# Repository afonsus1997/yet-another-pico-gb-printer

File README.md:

# Yet Another Pico GB Printer

## Acknowledgements 
Based on the [The-TinyGB-Printer](https://github.com/Raphael-Boichot/The-TinyGB-Printer) by [Raphael-Boichot](https://github.com/Raphael-Boichot)

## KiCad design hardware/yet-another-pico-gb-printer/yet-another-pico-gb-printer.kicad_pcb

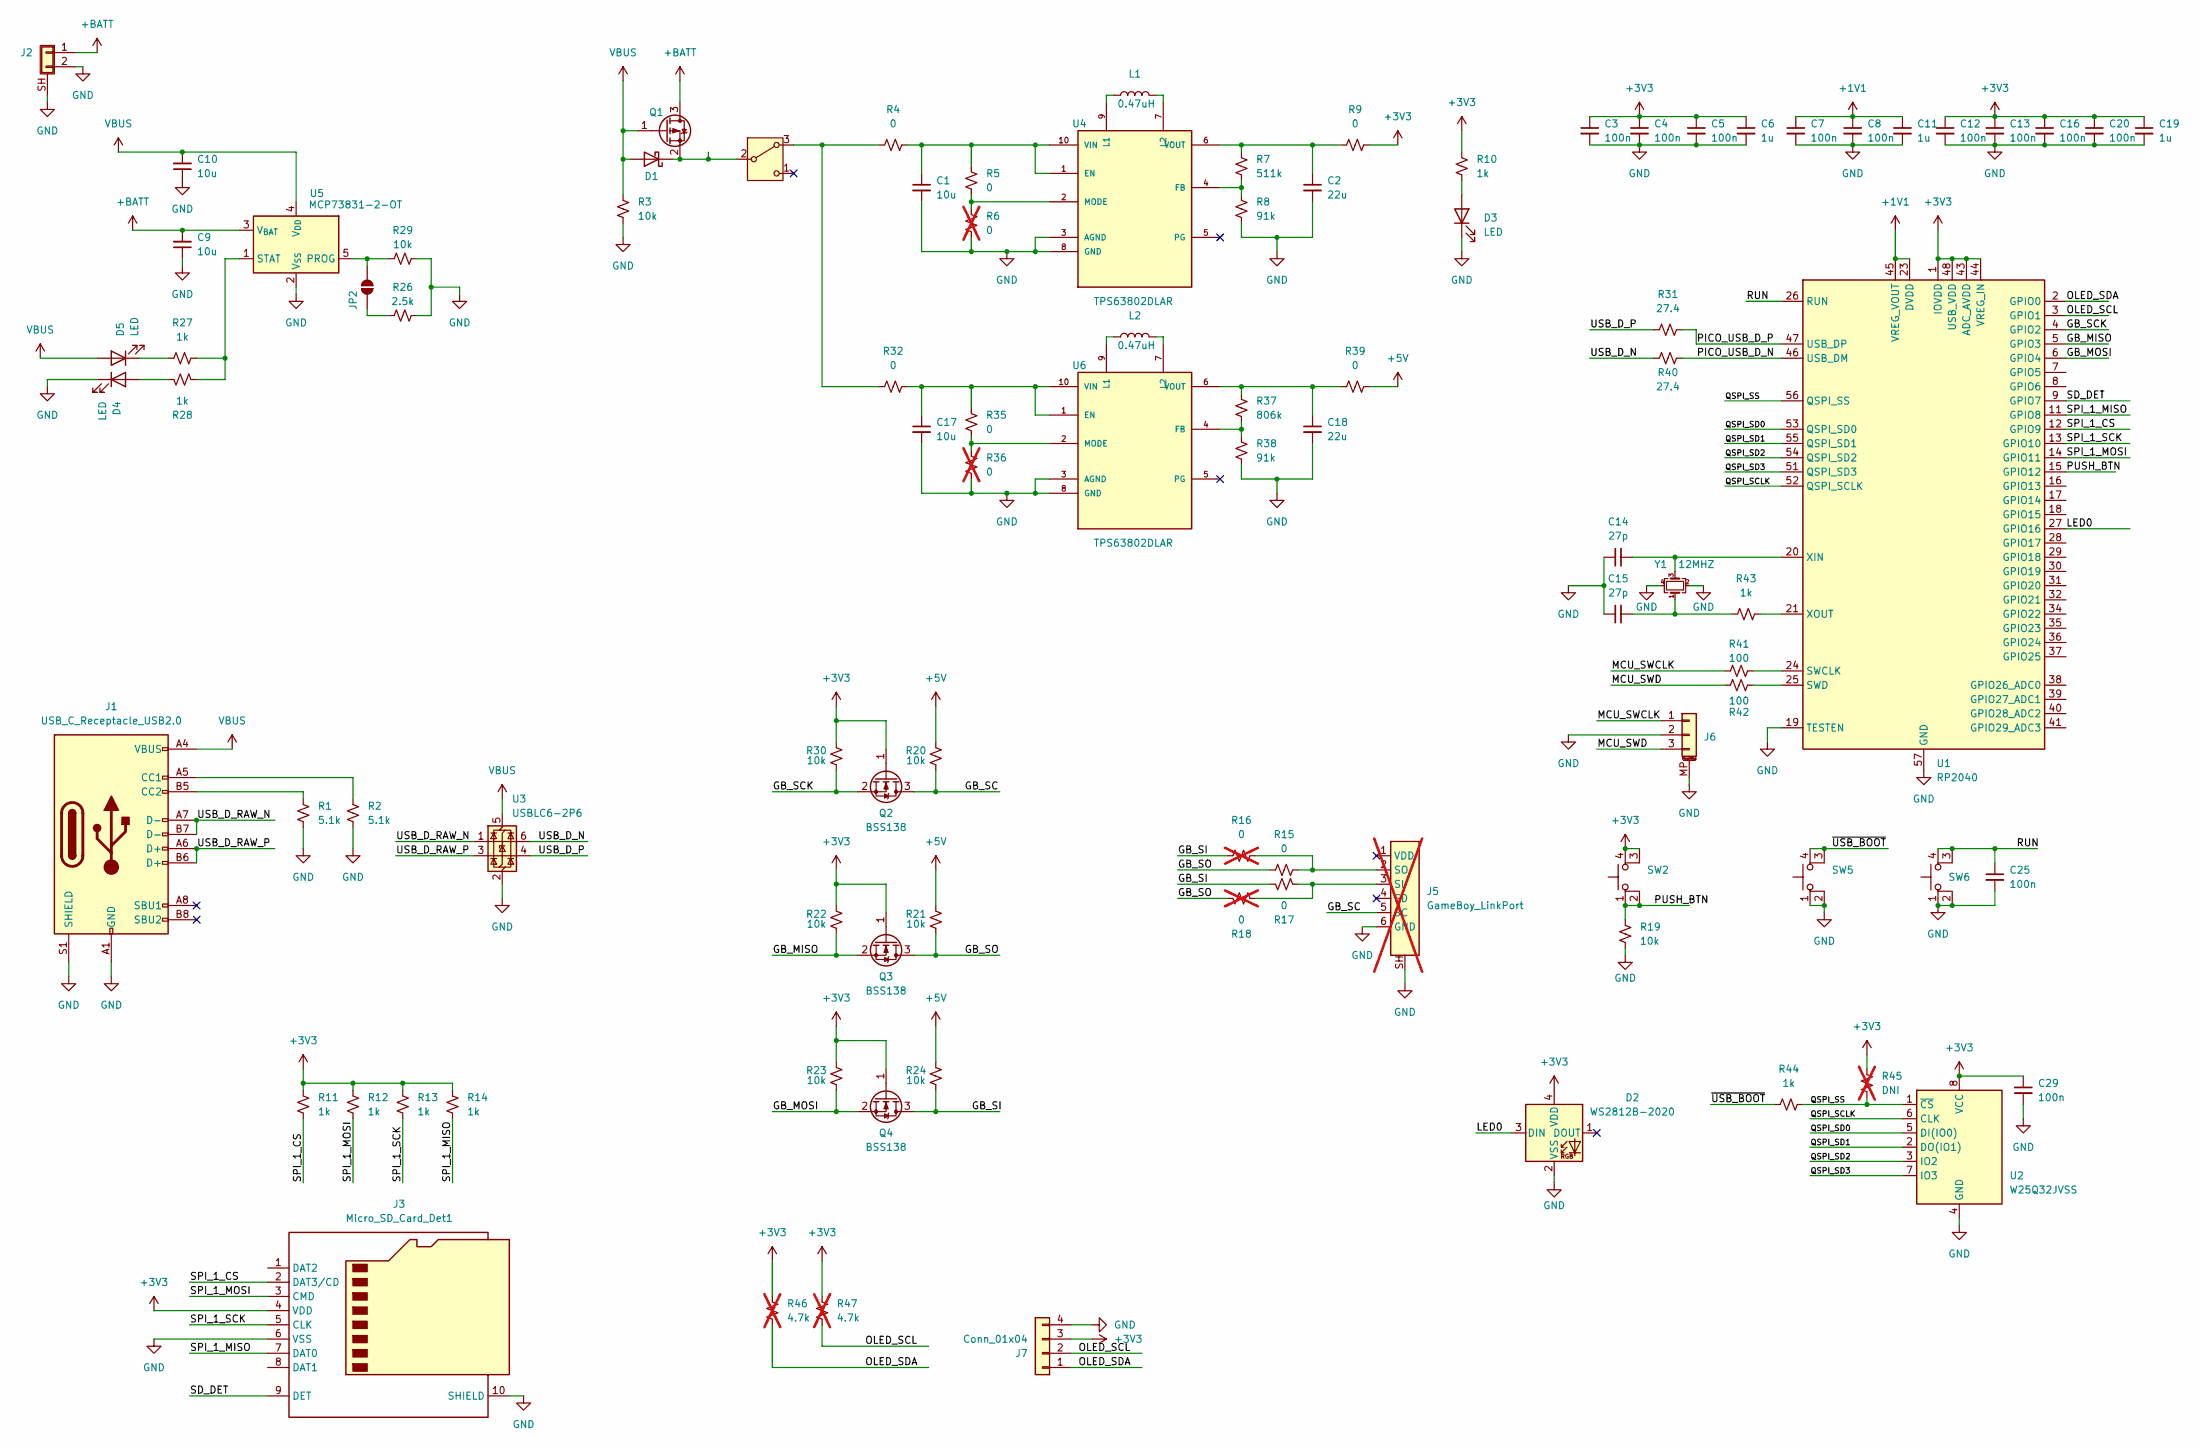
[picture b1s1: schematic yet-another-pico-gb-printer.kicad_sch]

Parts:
C1, C9, C10, C17: 10u; C_0603_1608Metric; LCSC C95839
C2, C18: 22u; C_0603_1608Metric; LCSC C59461
C3, C4, C5, C7, C8, C12, C13, C16, C20, C29: 100n; C_0402_1005Metric; LCSC C60474
C6, C11, C19: 1u; C_0402_1005Metric; LCSC C14445
C14, C15: 27p; C_0603_1608Metric; LCSC C107002
C25: 100n; C_0603_1608Metric; LCSC C60474
D1: D_Schottky; D_SOD-123F; LCSC C50553
D2: WS2812B-2020; LED_WS2812B-2020_PLCC4_2.0x2.0mm; LCSC C965555
D3, D4, D5: LED; LED_0603_1608Metric; LCSC C434424
J1: USB_C_Receptacle_USB2.0; USB_C_Receptacle_HCTL_HC-TYPE-C-16P-01A; LCSC C2894897
J2: Conn_01x02_Shielded; CONN-SMD_P2.00_S2B-PH-SM4-TB-LF-SN; LCSC C295747
J3: Micro_SD_Card_Det1; J_sd_micro_socket_no_holes; LCSC C7529389
J5: GameBoy_LinkPort; GBA-LINK; not fitted
J6: Conn_01x03_MountingPin; JST_SH_SM03B-SRSS-TB_1x03-1MP_P1.00mm_Horizontal; LCSC C160403
J7: Conn_01x04; OLED_SSD1306_128x32_0.91
JP2: SolderJumper_2_Open; SolderJumper-2_P1.3mm_Open_Pad1.0x1.5mm
L1, L2: 0.47uH; L_Wurth_WE-LQSH-2010; LCSC C89446
Q1: DMG3415U; SOT-23; LCSC C96616
Q2, Q3, Q4: BSS138; SOT-23; LCSC C5337205
R1, R2: 5.1k; R_0402_1005Metric; LCSC C105872
R3, R19, R20, R21, R22, R23, R24, R29, R30: 10k; R_0402_1005Metric; LCSC C60490
R4, R5, R9, R15, R17, R32, R35, R39: 0; R_0402_1005Metric; LCSC C106231
R6, R16, R18, R36: 0; R_0402_1005Metric; LCSC C106231; not fitted
R7: 511k; R_0402_1005Metric; LCSC C5126239
R8, R38: 91k; R_0402_1005Metric; LCSC C852952
R10, R11, R12, R13, R14, R27, R28, R43, R44: 1k; R_0402_1005Metric; LCSC C11702
R26: 2.5k; R_0402_1005Metric; LCSC C145071
R31, R40: 27.4; R_0402_1005Metric; LCSC C172043
R37: 806k; R_0402_1005Metric; LCSC C3016043
R41, R42: 100; R_0402_1005Metric; LCSC C25076
R45: DNI; R_0402_1005Metric; not fitted
R46, R47: 4.7k; R_0603_1608Metric; LCSC C99782; not fitted
SW2: SW_MEC_5E; SW-SMD_4P-L5.2-W5.2-P3.70-LS6.4; LCSC C2686853
SW3: SW_SPDT_321; SW-SMD_K3-1280S-L1; LCSC C223845
SW5, SW6: SW_MEC_5E; SW_SKRPACE010; LCSC C139797
U1: RP2040; QFN-56-1EP_7x7mm_P0.4mm_EP3.2x3.2mm; LCSC C2040
U2: W25Q32JVSS; Winbond_USON-8-1EP_3x2mm_P0.5mm_EP0.2x1.6mm; LCSC C2843335
U3: USBLC6-2P6; SOT-666; LCSC C2827693
U4, U6: TPS63802DLAR; VREG_TPS63802DLAR; PARTREV B; LCSC C2845237
U5: MCP73831-2-OT; SOT-23-5; LCSC C625600
Y1: 12MHZ; Crystal_SMD_3225-4Pin_3.2x2.5mm; LCSC C5182760

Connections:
+1V1: C7.1, C8.1, C11.1, U1.23 (DVDD), U1.45 (VREG_VOUT), U1.50 (DVDD)
+3V3: C3.1, C4.1, C5.1, C6.1, C12.1, C13.1, C16.1, C19.1, C20.1, C29.1, D2.4 (VDD), J3.4 (VDD), J7.3, Q2.1 (G), Q3.1 (G), Q4.1 (G), R9.2, R10.2, R11.2, R12.2, R13.2, R14.2, R22.1, R23.1, R30.1, R45.1, R46.1, R47.1, SW2.3 (K), SW2.4 (A), U1.1 (IOVDD), U1.10 (IOVDD), U1.22 (IOVDD), U1.33 (IOVDD), U1.42 (IOVDD), U1.43 (ADC_AVDD), U1.44 (VREG_IN), U1.48 (USB_VDD), U1.49 (IOVDD), U2.8 (VCC)
+5V: R20.1, R21.1, R24.1, R39.2
+BATT: C9.2, J2.1, Q1.3 (D), U5.3 (V_{BAT})
/GB_MISO: Q3.2 (S), R22.2, U1.5 (GPIO3)
/GB_MOSI: Q4.2 (S), R23.2, U1.6 (GPIO4)
/GB_SC: J5.5 (SC), Q2.3 (D), R20.2
/GB_SCK: Q2.2 (S), R30.2, U1.4 (GPIO2)
/GB_SI: Q4.3 (D), R16.1, R17.1, R24.2
/GB_SO: Q3.3 (D), R15.1, R18.1, R21.2
/LED0: D2.3 (DIN), U1.27 (GPIO16)
/MCU_SWCLK: J6.1, R41.1
/MCU_SWD: J6.3, R42.1
/OLED_SCL: J7.2, R47.2, U1.3 (GPIO1)
/OLED_SDA: J7.1, R46.2, U1.2 (GPIO0)
/PICO_USB_D_N: R40.2, U1.46 (USB_DM)
/PICO_USB_D_P: R31.2, U1.47 (USB_DP)
/PUSH_BTN: R19.1, SW2.1, SW2.2, U1.15 (GPIO12)
/QSPI_SCLK: U1.52 (QSPI_SCLK), U2.6 (CLK)
/QSPI_SD0: U1.53 (QSPI_SD0), U2.5 (DI(IO0))
/QSPI_SD1: U1.55 (QSPI_SD1), U2.2 (DO(IO1))
/QSPI_SD2: U1.54 (QSPI_SD2), U2.3 (IO2)
/QSPI_SD3: U1.51 (QSPI_SD3), U2.7 (IO3)
/QSPI_SS: R44.2, R45.2, U1.56 (QSPI_SS), U2.1 (~CS)
/RUN: C25.1, SW6.3 (K), SW6.4 (A), U1.26 (RUN)
/SD_DET: J3.9 (DET), U1.9 (GPIO7)
/SPI_1_CS: J3.2 (DAT3/CD), R11.1, U1.12 (GPIO9)
/SPI_1_MISO: J3.7 (DAT0), R14.1, U1.11 (GPIO8)
/SPI_1_MOSI: J3.3 (CMD), R12.1, U1.14 (GPIO11)
/SPI_1_SCK: J3.5 (CLK), R13.1, U1.13 (GPIO10)
/USB_D_N: R40.1, U3.6 (I/O1)
/USB_D_P: R31.1, U3.4 (I/O2)
/USB_D_RAW_N: J1.A7 (D-), J1.B7 (D-), U3.1 (I/O1)
/USB_D_RAW_P: J1.A6 (D+), J1.B6 (D+), U3.3 (I/O2)
/~USB_BOOT: R44.1, SW5.3 (K), SW5.4 (A)
GND: C1.2, C2.2, C3.2, C4.2, C5.2, C6.2, C7.2, C8.2, C9.1, C10.1, C11.2, C12.2, C13.2, C14.1, C15.1, C16.2, C17.2, C18.2, C19.2, C20.2, C25.2, C29.2, D2.2 (VSS), D3.1 (K), D4.1 (K), J1.A1 (GND), J1.A12 (GND), J1.B1 (GND), J1.B12 (GND), J1.S1 (SHIELD), J2.2, J2.SH (Shield), J3.6 (VSS), J3.10 (SHIELD), J5.6 (GND), J5.SH, J6.2, J6.MP (MountPin), J7.4, R1.2, R2.2, R3.2, R6.1, R8.2, R19.2, R26.1, R29.1, R36.1, R38.2, SW5.1, SW5.2, SW6.1, SW6.2, U1.19 (TESTEN), U1.57 (GND), U2.4 (GND), U3.2 (GND), U4.3 (AGND), U4.8 (GND), U5.2 (V_{SS}), U6.3 (AGND), U6.8 (GND), Y1.2, Y1.4
unnamed: C15.2, R43.1, Y1.1
unnamed: D1.1 (K), Q1.2 (S), SW3.2 (B)
unnamed: D3.2 (A), R10.1
unnamed: D4.2 (A), R28.2
unnamed: D5.1 (K), R27.2
unnamed: J1.A5 (CC1), R2.1
unnamed: J1.B5 (CC2), R1.1
unnamed: J5.3 (SI), R17.2, R18.2
unnamed: J5.2 (SO), R15.2, R16.2
unnamed: JP2.1 (A), R26.2
unnamed: JP2.2 (B), R29.2, U5.5 (PROG)
unnamed: R4.1, R32.1, SW3.3 (A)
unnamed: R41.2, U1.24 (SWCLK)
unnamed: R42.2, U1.25 (SWD)
unnamed: C14.2, U1.20 (XIN), Y1.3
unnamed: R43.2, U1.21 (XOUT)
unnamed: C1.1, R4.2, R5.2, U4.1 (EN), U4.10 (VIN)
unnamed: R7.2, R8.1, U4.4 (FB)
unnamed: L1.1, U4.9 (L1)
unnamed: L1.2, U4.7 (L2)
unnamed: R5.1, R6.2, U4.2 (MODE)
unnamed: C2.1, R7.1, R9.1, U4.6 (VOUT)
unnamed: R27.1, R28.1, U5.1 (STAT)
unnamed: C17.1, R32.2, R35.2, U6.1 (EN), U6.10 (VIN)
unnamed: R37.2, R38.1, U6.4 (FB)
unnamed: L2.1, U6.9 (L1)
unnamed: L2.2, U6.7 (L2)
unnamed: R35.1, R36.2, U6.2 (MODE)
unnamed: C18.1, R37.1, R39.1, U6.6 (VOUT)
VBUS: C10.2, D1.2 (A), D5.2 (A), J1.A4 (VBUS), J1.A9 (VBUS), J1.B4 (VBUS), J1.B9 (VBUS), Q1.1 (G), R3.1, U3.5 (VBUS), U5.4 (V_{DD})

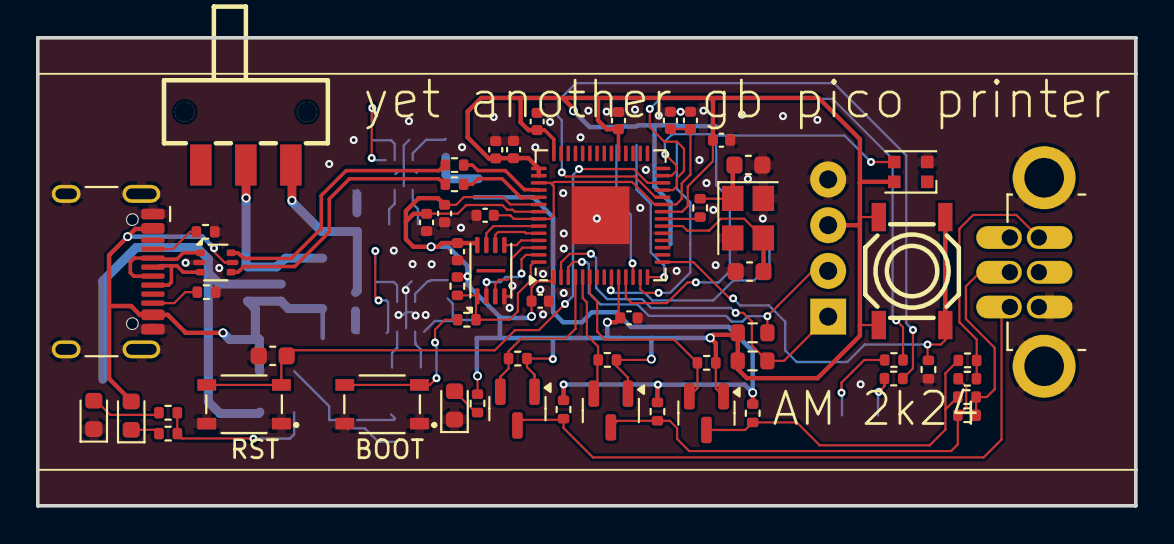
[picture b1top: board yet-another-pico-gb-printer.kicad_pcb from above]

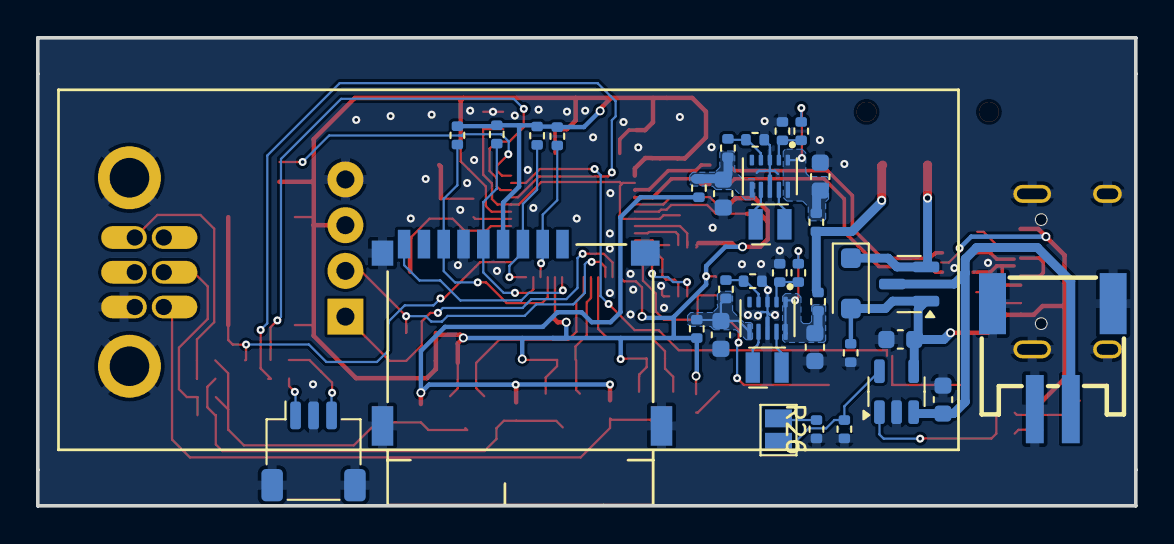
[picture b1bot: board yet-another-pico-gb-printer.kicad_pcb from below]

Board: 4 copper layers, 61.0 x 26.0 mm, 95 parts (36 on the bottom side), 66 nets.

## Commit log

2024-12-11 added libs and schematic
2024-12-12 more schematic and layout
2024-12-12 changed project name
2024-12-12 removed old project
2024-12-12 added library submodule
2024-12-12 schematics and layout improvements
2024-12-13 sent to fab
2024-12-13 minor changes for jlc
2024-12-14 started working on software
2025-09-15 minor code fixes
2025-09-15 started adding gprinter stuff
